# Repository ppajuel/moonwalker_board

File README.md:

# moonwalker_board
Expansion board compatible with [Raspberry Pi 1 Modelo B](https://www.raspberrypi.org/products/model-b/)
 and [IGEP NEW YORK](https://isee.biz/products/igep-expansion-boards/igep-new-york) to control a RC CAR. Board Layout has been adapted to suite with [Nikko Mega Dominator](http://nikkoevolution.fr/voitures_et_pieces/568/Nikko-Mega-Dominator.html), but can be easily adaptable to another RC Car. Its features are:

* ATmega328 microcontroller: control all expansion board functionalities.
* Raspberry or IGEP boards (optional): control microcontroller through serial port.
* GPS expansion bus: [Adafruit Ultimate GPS Breakout](https://www.adafruit.com/product/746).
* Compass and accelerometer expansion bus: [Triple-axis Accelerometer+Magnetometer (Compass) Board - LSM303)](https://www.adafruit.com/product/1120).
* Gauge battery circuit.
* Servo and brushed motor drivers.
* Two independent power trees for electric motors and sensors&control.
* Atmega programer header.
* Hex segment display.

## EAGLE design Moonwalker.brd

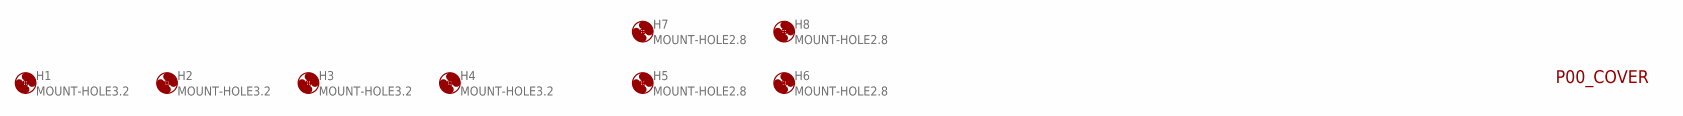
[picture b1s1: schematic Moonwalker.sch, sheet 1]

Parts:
H1, H2, H3, H4: MOUNT-HOLE3.2; 3,2
H5, H6, H7, H8: MOUNT-HOLE2.8; 2,8

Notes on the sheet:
P00_COVER

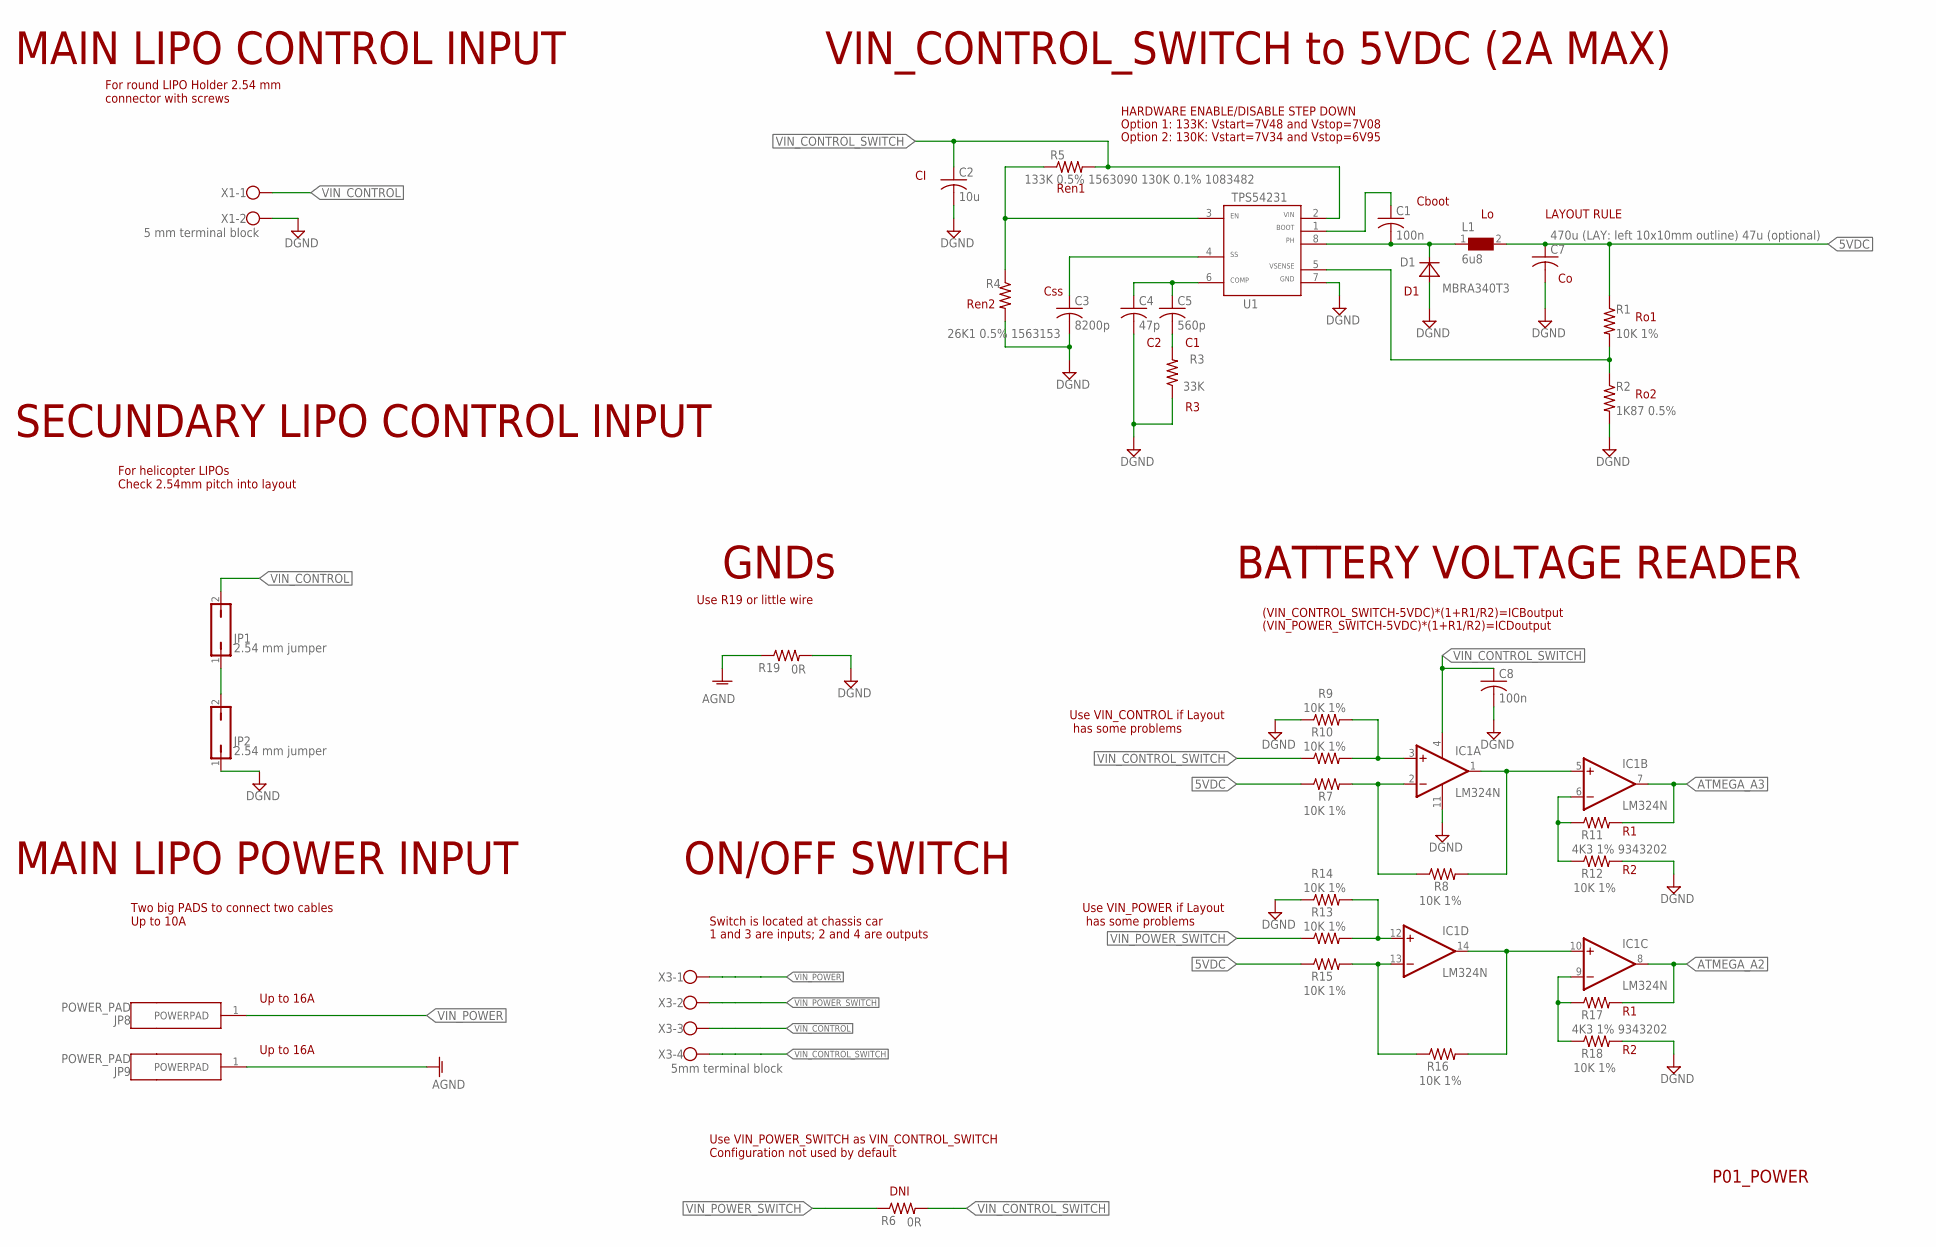
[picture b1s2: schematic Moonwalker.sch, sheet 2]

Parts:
C1: 100n; C075-032X103
C2: 10u; C025-050X050
C3: 8200p; C1206
C4: 47p; C050-024X044
C5: 560p; C1206
C7: 470u (LAY: left 10x10mm outline) 47u (optional); C050-075X075
C8: 100n; C050-024X044
D1: MBRA340T3; SMA
IC1: LM324N; DIL14
JP1, JP2: 2.54 mm jumper; JP1
JP8, JP9: POWER_PAD
L1: 6u8; WE-PD_7332/7345_PLASTIC_BASE
R1, R7, R8, R9, R10, R12, R13, R14, R15, R16, R18: 10K 1%; 0309/10
R2: 1K87 0.5%; 0309/10
R3: 33K; 0309/10
R4: 26K1 0.5% 1563153; 0309/10
R5: 133K 0.5% 1563090 130K 0.1% 1083482; 0309/10
R6, R19: 0R; 0309/10
R11, R17: 4K3 1% 9343202; 0309/10
U1: TPS54231SO8; SO8
X1: 5 mm terminal block; W237-102
X3: 5mm terminal block; W237-4

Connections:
5VDC: C7.1, L1.2, R1.1, R7.1, R15.1; also elsewhere on the board
AGND: JP9.1, R19.1; also elsewhere on the board
ATMEGA_A2: IC1.8 (OUT), R17.2; also elsewhere on the board
ATMEGA_A3: IC1.7 (OUT), R11.2; also elsewhere on the board
DGND: C2.2, C3.2, C4.2, C7.2, C8.2, D1.A, IC1.11 (V-), JP2.1, R2.2, R3.1, R4.2, R9.1, R12.2, R14.1, R18.2, R19.2, U1.7, X1.2; also elsewhere on the board
unnamed: C4.1, C5.1, U1.6
unnamed: C5.2, R3.2
unnamed: R4.1, R5.1, U1.3
unnamed: C3.1, U1.4
unnamed: C1.2, D1.C, L1.1, U1.8
unnamed: C1.1, U1.1
unnamed: R1.2, R2.1, U1.5
unnamed: JP1.1, JP2.2
unnamed: IC1.3 (+IN), R9.2, R10.2
unnamed: IC1.2 (-IN), R7.2, R8.1
unnamed: IC1.12 (+IN), R13.2, R14.2
unnamed: IC1.13 (-IN), R15.2, R16.1
unnamed: IC1.10 (+IN), IC1.14 (OUT), R16.2
unnamed: IC1.1 (OUT), IC1.5 (+IN), R8.2
unnamed: IC1.6 (-IN), R11.1, R12.1
unnamed: IC1.9 (-IN), R17.1, R18.1
VIN_CONTROL: JP1.2, X1.1, X3.3
VIN_CONTROL_SWITCH: C2.1, C8.1, IC1.4 (V+), R5.2, R6.2, R10.1, U1.2, X3.4
VIN_POWER: JP8.1, X3.1; also elsewhere on the board
VIN_POWER_SWITCH: R6.1, R13.1, X3.2

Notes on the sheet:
P01_POWER
Cboot
VIN_CONTROL_SWITCH to 5VDC (2A MAX)
Option 2: 130K: Vstart=7V34 and Vstop=6V95
Option 1: 133K: Vstart=7V48 and Vstop=7V08
HARDWARE ENABLE/DISABLE STEP DOWN
Ren2
Ren1
Css
Ro1
Ro2
MAIN LIPO CONTROL INPUT
SECUNDARY LIPO CONTROL INPUT
For round LIPO Holder 2.54 mm connector with screws
For helicopter LIPOs Check 2.54mm pitch into layout
MAIN LIPO POWER INPUT
Two big PADS to connect two cables Up to 10A
Use VIN_POWER_SWITCH as VIN_CONTROL_SWITCH Configuration not used by default
DNI
BATTERY VOLTAGE READER
ON/OFF SWITCH
(VIN_CONTROL_SWITCH-5VDC)*(1+R1/R2)=ICBoutput
(VIN_POWER_SWITCH-5VDC)*(1+R1/R2)=ICDoutput
GNDs
Switch is located at chassis car
Use VIN_POWER if Layout has some problems
Use VIN_CONTROL if Layout has some problems
Up to 16A
LAYOUT RULE
Use R19 or little wire
1 and 3 are inputs; 2 and 4 are outputs

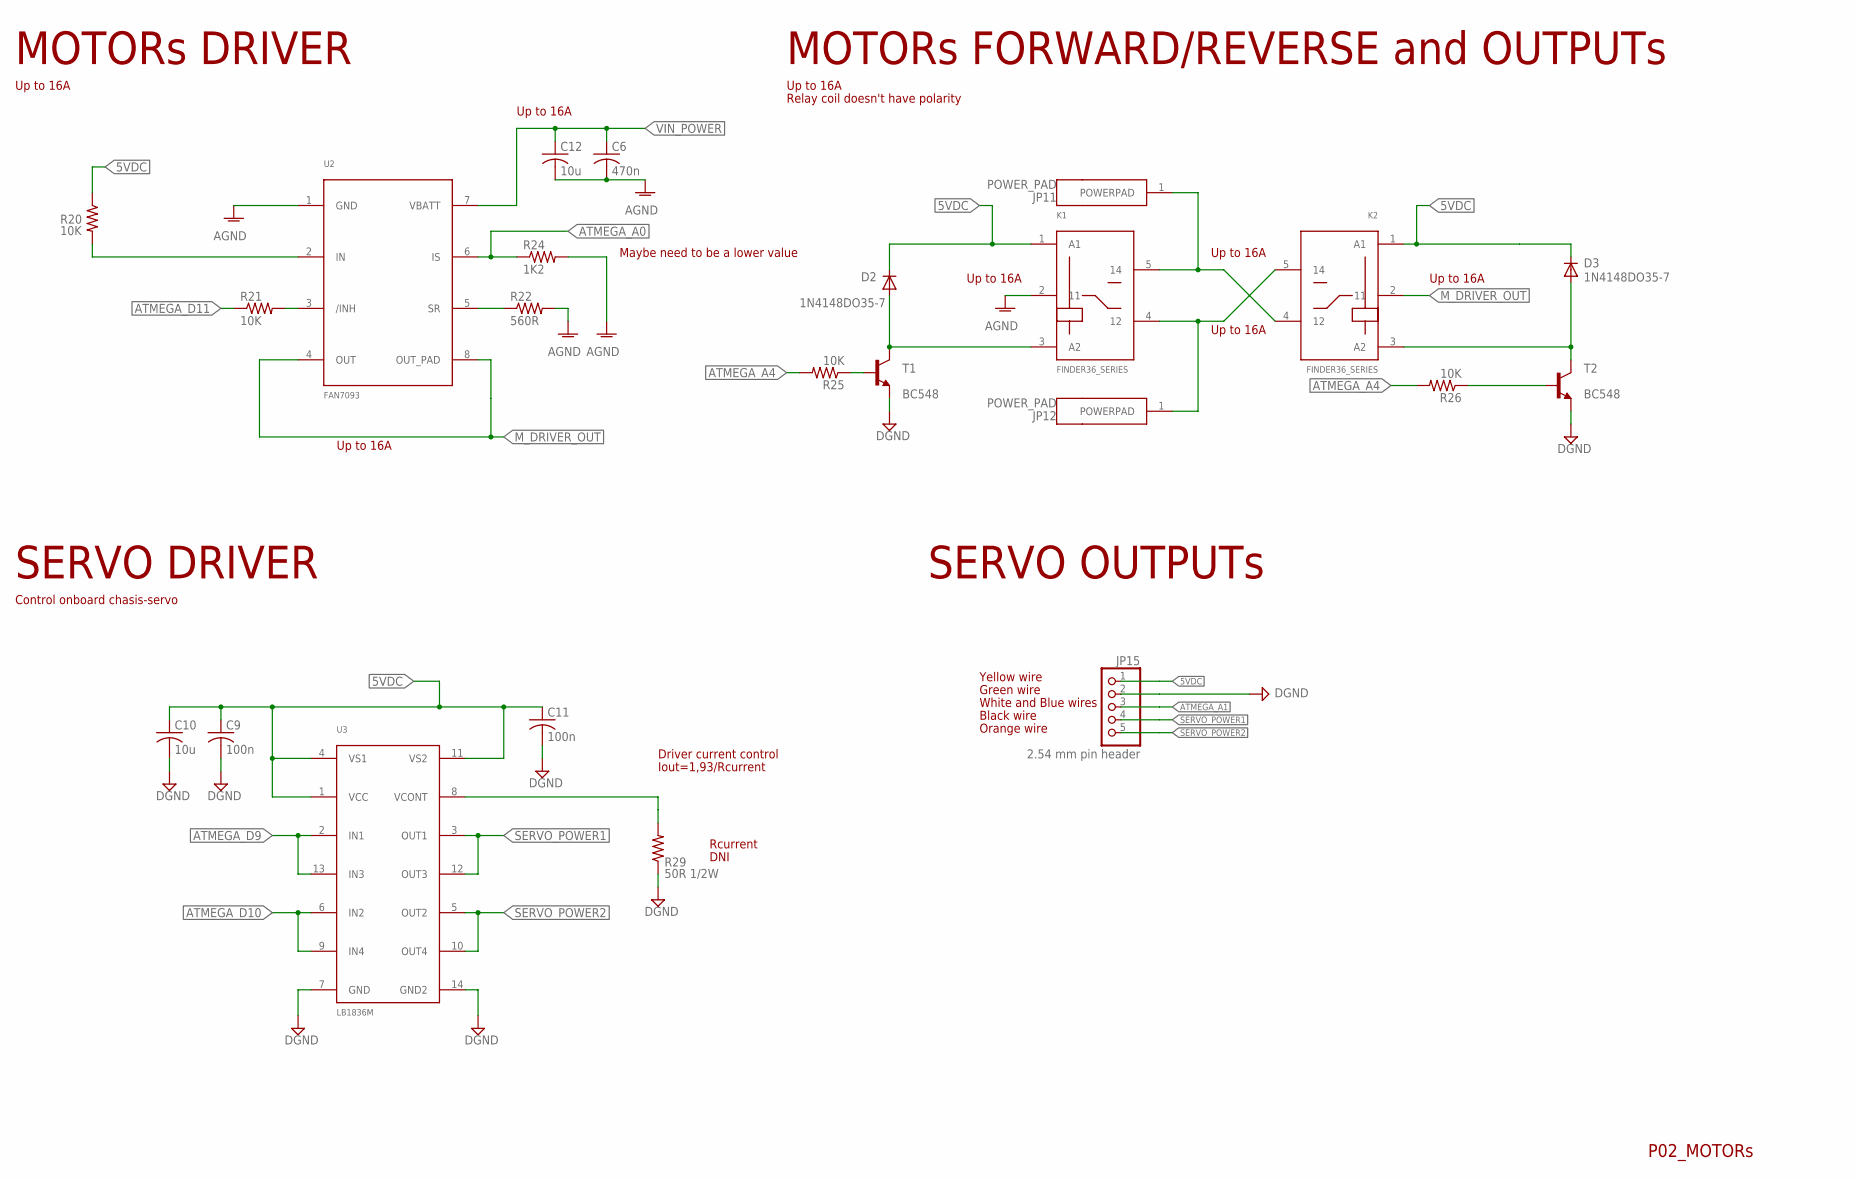
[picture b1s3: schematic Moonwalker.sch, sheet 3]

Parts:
C6: 470n; C050-050X075
C9, C11: 100n; C050-024X044
C10, C12: 10u; C025-050X050
D2, D3: 1N4148DO35-7; DO35-7
JP11, JP12: POWER_PAD
JP15: 2.54 mm pin header; 1X05/90
K1, K2: FINDER36_SERIES; FINDERSERIE36
R20, R21, R25, R26: 10K; 0309/10
R22: 560R; 0309/10
R24: 1K2; 0411/12
R29: 50R 1/2W; 0411/12
T1, T2: BC548; TO92-CBE
U2: FAN7093; TO263
U3: LB1836M; SOIC14W

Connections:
5VDC: C9.1, C10.1, C11.1, D2.C, D3.C, JP15.1, K1.1 (A1), K2.1 (A1), R20.1, U3.1 (VCC), U3.4 (VS1), U3.11 (VS2); also elsewhere on the board
AGND: C6.2, C12.2, K1.2 (11), R22.2, R24.2, U2.1 (GND); also elsewhere on the board
ATMEGA_A0: R24.1, U2.6 (IS); also elsewhere on the board
ATMEGA_A1: JP15.3; also elsewhere on the board
ATMEGA_A4: R25.2, R26.2; also elsewhere on the board
ATMEGA_D9: U3.2 (IN1), U3.13 (IN3); also elsewhere on the board
ATMEGA_D10: U3.6 (IN2), U3.9 (IN4); also elsewhere on the board
ATMEGA_D11: R21.1; also elsewhere on the board
DGND: C9.2, C10.2, C11.2, JP15.2, R29.1, T1.E, T2.E, U3.7 (GND), U3.14 (GND2); also elsewhere on the board
M_DRIVER_OUT: K2.2 (11), U2.4 (OUT), U2.8 (OUT_PAD)
unnamed: R29.2, U3.8 (VCONT)
unnamed: JP11.1, K1.5 (14), K2.4 (12)
unnamed: R22.1, U2.5 (SR)
unnamed: R20.2, U2.2 (IN)
unnamed: R21.2, U2.3 (/INH)
unnamed: JP12.1, K1.4 (12), K2.5 (14)
unnamed: D2.A, K1.3 (A2), T1.C
unnamed: D3.A, K2.3 (A2), T2.C
unnamed: R26.1, T2.B
unnamed: R25.1, T1.B
SERVO_POWER1: JP15.4, U3.3 (OUT1), U3.12 (OUT3)
SERVO_POWER2: JP15.5, U3.5 (OUT2), U3.10 (OUT4)
VIN_POWER: C6.1, C12.1, U2.7 (VBATT); also elsewhere on the board

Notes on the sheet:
P02_MOTORs
MOTORs DRIVER
Up to 16A
MOTORs FORWARD/REVERSE and OUTPUTs
SERVO DRIVER
Control onboard chasis-servo
Driver current control
Iout=1,93/Rcurrent
Rcurrent
DNI
SERVO OUTPUTs
Yellow wire
Green wire
White and Blue wires
Black wire
Orange wire
Maybe need to be a lower value
Relay coil doesn't have polarity

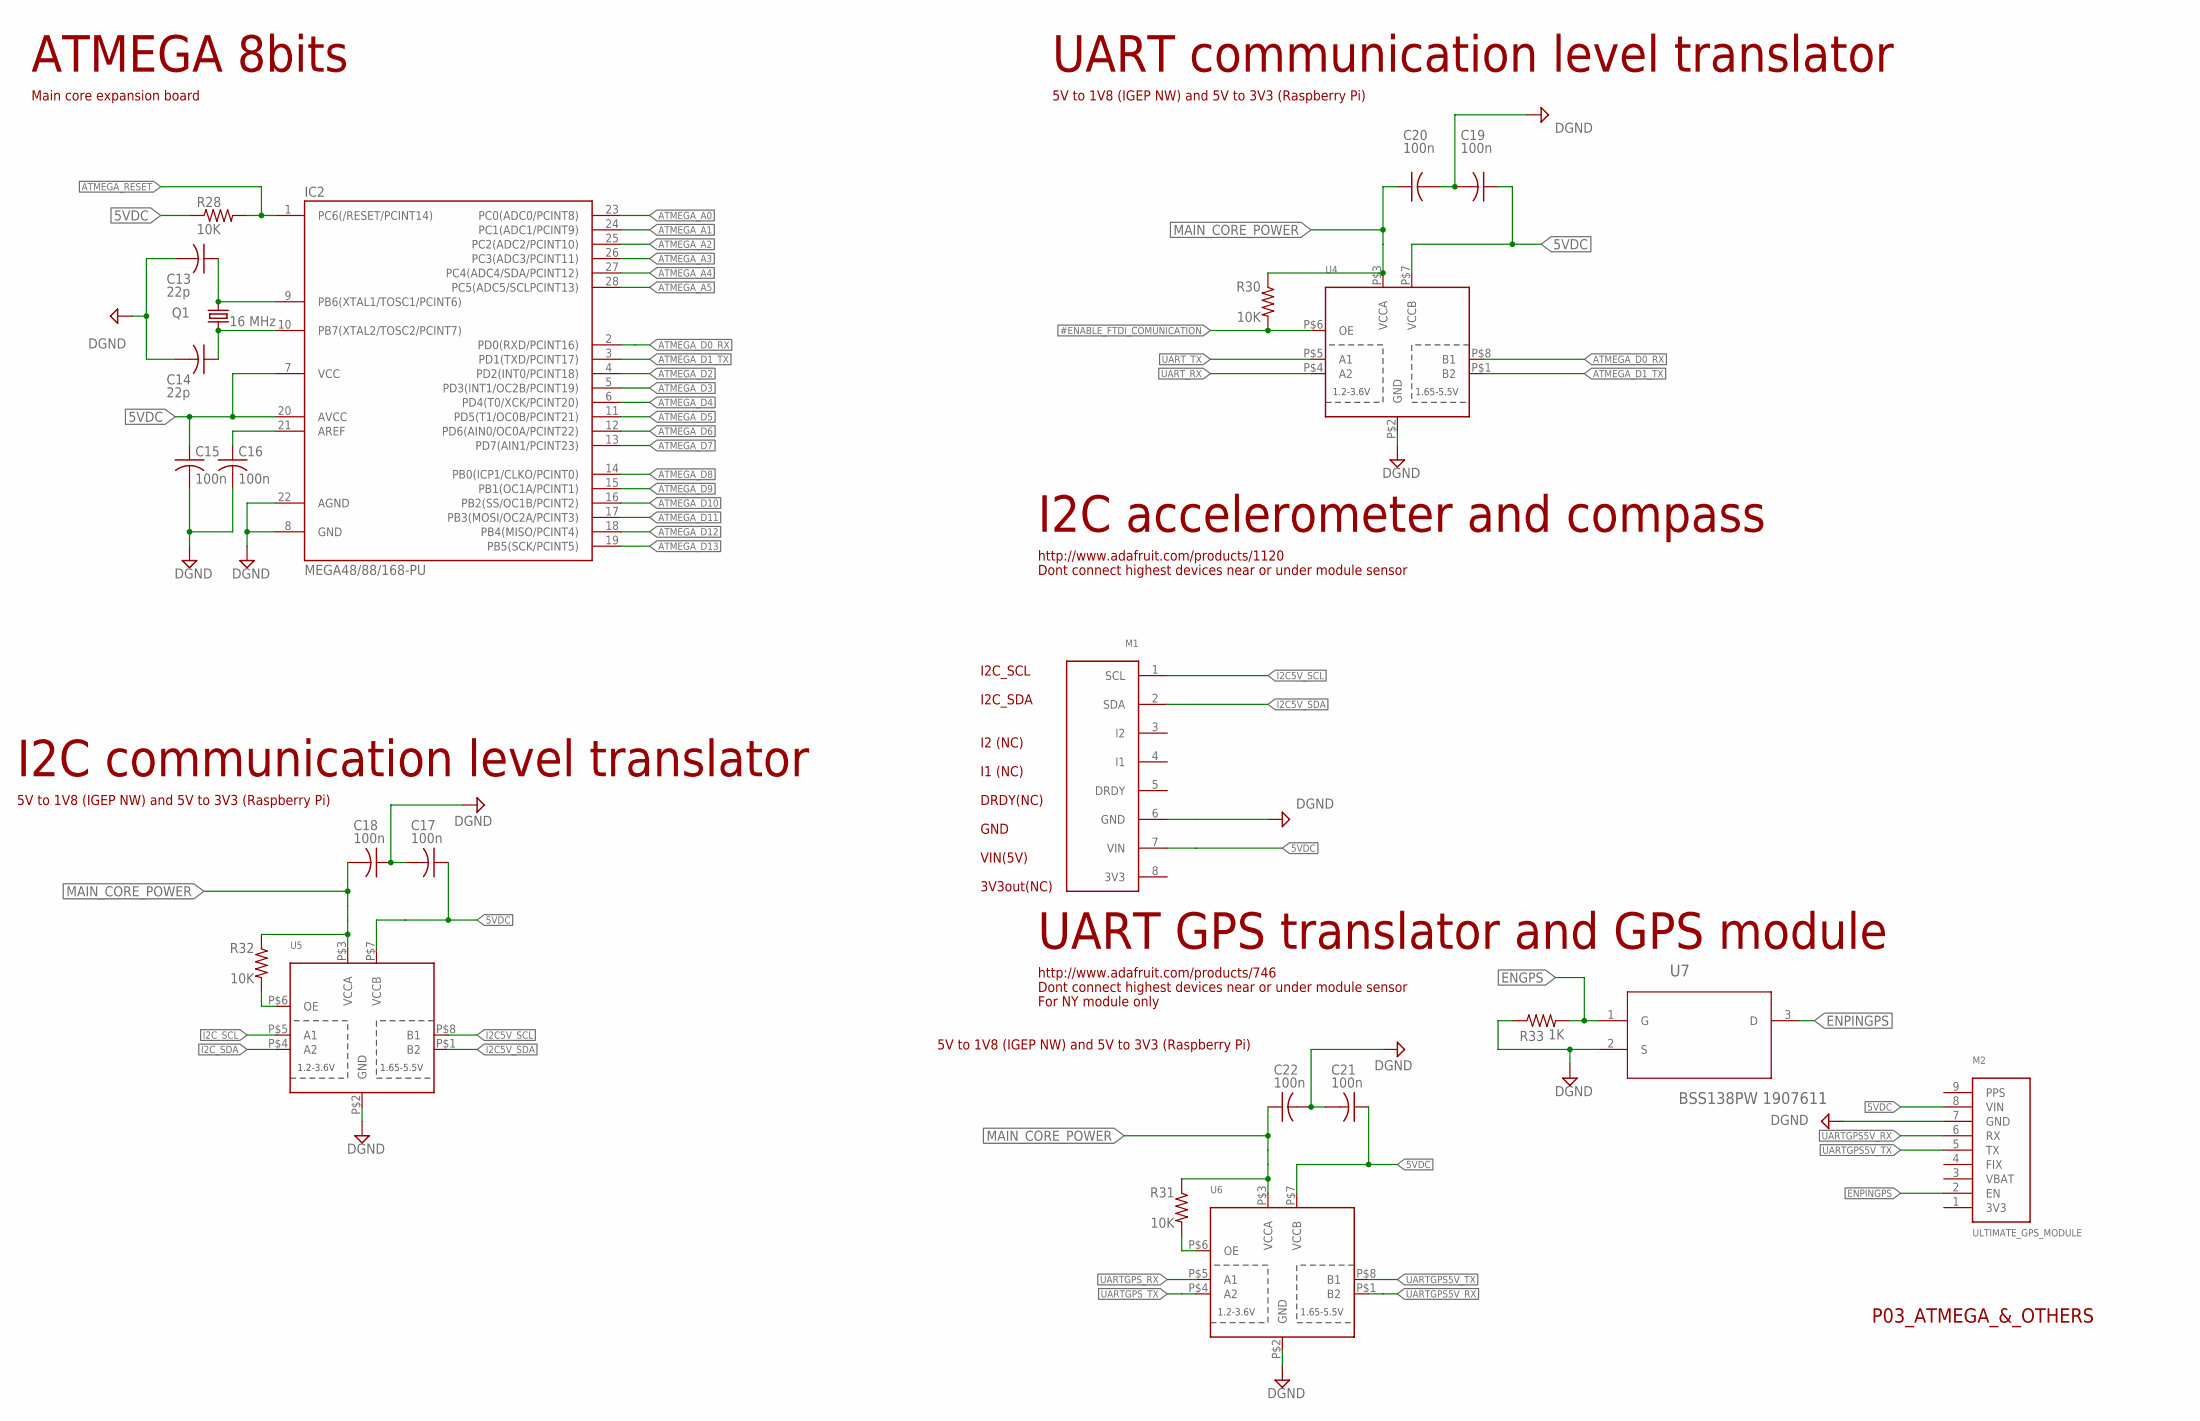
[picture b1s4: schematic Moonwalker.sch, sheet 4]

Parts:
C13, C14: 22p; C050-024X044
C15, C16, C17, C18, C19, C20, C21, C22: 100n; C050-024X044
IC2: MEGA48/88/168-PU; DIL28-3
M1: COMPASS_&_ACCELEROMETER_ADAFRUIT_LSM303
M2: ULTIMATE_GPS_MODULE
Q1: 16 MHz; HC49/S
R28, R30, R31, R32: 10K; 0309/10
R33: 1K; 0309/10
U4, U5, U6: TXS0102; VFSOP-8
U7: BSS138PW 1907611; SOT65P210X110-3N

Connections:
5VDC: C15.1, C17.1, C19.1, C21.1, IC2.7 (VCC), IC2.20 (AVCC), M1.7 (VIN), M2.8 (VIN), R28.1, U4.P$7 (VCCB), U5.P$7 (VCCB), U6.P$7 (VCCB); also elsewhere on the board
#ENABLE_FTDI_COMUNICATION: R30.2, U4.P$6 (OE); also elsewhere on the board
ATMEGA_A0: IC2.23 (PC0(ADC0/PCINT8)); also elsewhere on the board
ATMEGA_A1: IC2.24 (PC1(ADC1/PCINT9)); also elsewhere on the board
ATMEGA_A2: IC2.25 (PC2(ADC2/PCINT10)); also elsewhere on the board
ATMEGA_A3: IC2.26 (PC3(ADC3/PCINT11)); also elsewhere on the board
ATMEGA_A4: IC2.27 (PC4(ADC4/SDA/PCINT12)); also elsewhere on the board
ATMEGA_A5: IC2.28 (PC5(ADC5/SCLPCINT13)); also elsewhere on the board
ATMEGA_D0_RX: IC2.2 (PD0(RXD/PCINT16)), U4.P$8 (B1); also elsewhere on the board
ATMEGA_D1_TX: IC2.3 (PD1(TXD/PCINT17)), U4.P$1 (B2); also elsewhere on the board
ATMEGA_D2: IC2.4 (PD2(INT0/PCINT18)); also elsewhere on the board
ATMEGA_D3: IC2.5 (PD3(INT1/OC2B/PCINT19)); also elsewhere on the board
ATMEGA_D4: IC2.6 (PD4(T0/XCK/PCINT20)); also elsewhere on the board
ATMEGA_D5: IC2.11 (PD5(T1/OC0B/PCINT21)); also elsewhere on the board
ATMEGA_D6: IC2.12 (PD6(AIN0/OC0A/PCINT22)); also elsewhere on the board
ATMEGA_D7: IC2.13 (PD7(AIN1/PCINT23)); also elsewhere on the board
ATMEGA_D8: IC2.14 (PB0(ICP1/CLKO/PCINT0)); also elsewhere on the board
ATMEGA_D9: IC2.15 (PB1(OC1A/PCINT1)); also elsewhere on the board
ATMEGA_D10: IC2.16 (PB2(SS/OC1B/PCINT2)); also elsewhere on the board
ATMEGA_D11: IC2.17 (PB3(MOSI/OC2A/PCINT3)); also elsewhere on the board
ATMEGA_D12: IC2.18 (PB4(MISO/PCINT4)); also elsewhere on the board
ATMEGA_D13: IC2.19 (PB5(SCK/PCINT5)); also elsewhere on the board
ATMEGA_RESET: IC2.1 (PC6(/RESET/PCINT14)), R28.2; also elsewhere on the board
DGND: C13.2, C14.2, C15.2, C16.2, C17.2, C18.1, C19.2, C20.2, C21.2, C22.2, IC2.8 (GND), IC2.22 (AGND), M1.6 (GND), M2.7 (GND), R33.1, U4.P$2 (GND), U5.P$2 (GND), U6.P$2 (GND), U7.2 (S); also elsewhere on the board
ENGPS: R33.2, U7.1 (G); also elsewhere on the board
ENPINGPS: M2.2 (EN), U7.3 (D)
I2C5V_SCL: M1.1 (SCL), U5.P$8 (B1)
I2C5V_SDA: M1.2 (SDA), U5.P$1 (B2)
I2C_SCL: U5.P$5 (A1); also elsewhere on the board
I2C_SDA: U5.P$4 (A2); also elsewhere on the board
MAIN_CORE_POWER: C18.2, C20.1, C22.1, R30.1, R31.1, R32.1, U4.P$3 (VCCA), U5.P$3 (VCCA), U6.P$3 (VCCA); also elsewhere on the board
unnamed: C13.1, IC2.9 (PB6(XTAL1/TOSC1/PCINT6)), Q1.2
unnamed: C14.1, IC2.10 (PB7(XTAL2/TOSC2/PCINT7)), Q1.1
unnamed: C16.1, IC2.21 (AREF)
unnamed: R32.2, U5.P$6 (OE)
unnamed: R31.2, U6.P$6 (OE)
UARTGPS5V_RX: M2.6 (RX), U6.P$1 (B2)
UARTGPS5V_TX: M2.5 (TX), U6.P$8 (B1)
UARTGPS_RX: U6.P$5 (A1); also elsewhere on the board
UARTGPS_TX: U6.P$4 (A2); also elsewhere on the board
UART_RX: U4.P$4 (A2); also elsewhere on the board
UART_TX: U4.P$5 (A1); also elsewhere on the board

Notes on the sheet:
P03_ATMEGA_&_OTHERS
ATMEGA 8bits
Main core expansion board
UART communication level translator
5V to 1V8 (IGEP NW) and 5V to 3V3 (Raspberry Pi)
I2C communication level translator
I2C accelerometer and compass
http://www.adafruit.com/products/1120
Dont connect highest devices near or under module sensor
I2C_SCL
I2C_SDA
I2 (NC)
I1 (NC)
DRDY(NC)
GND
VIN(5V)
3V3out(NC)
UART GPS translator and GPS module
http://www.adafruit.com/products/746
For NY module only

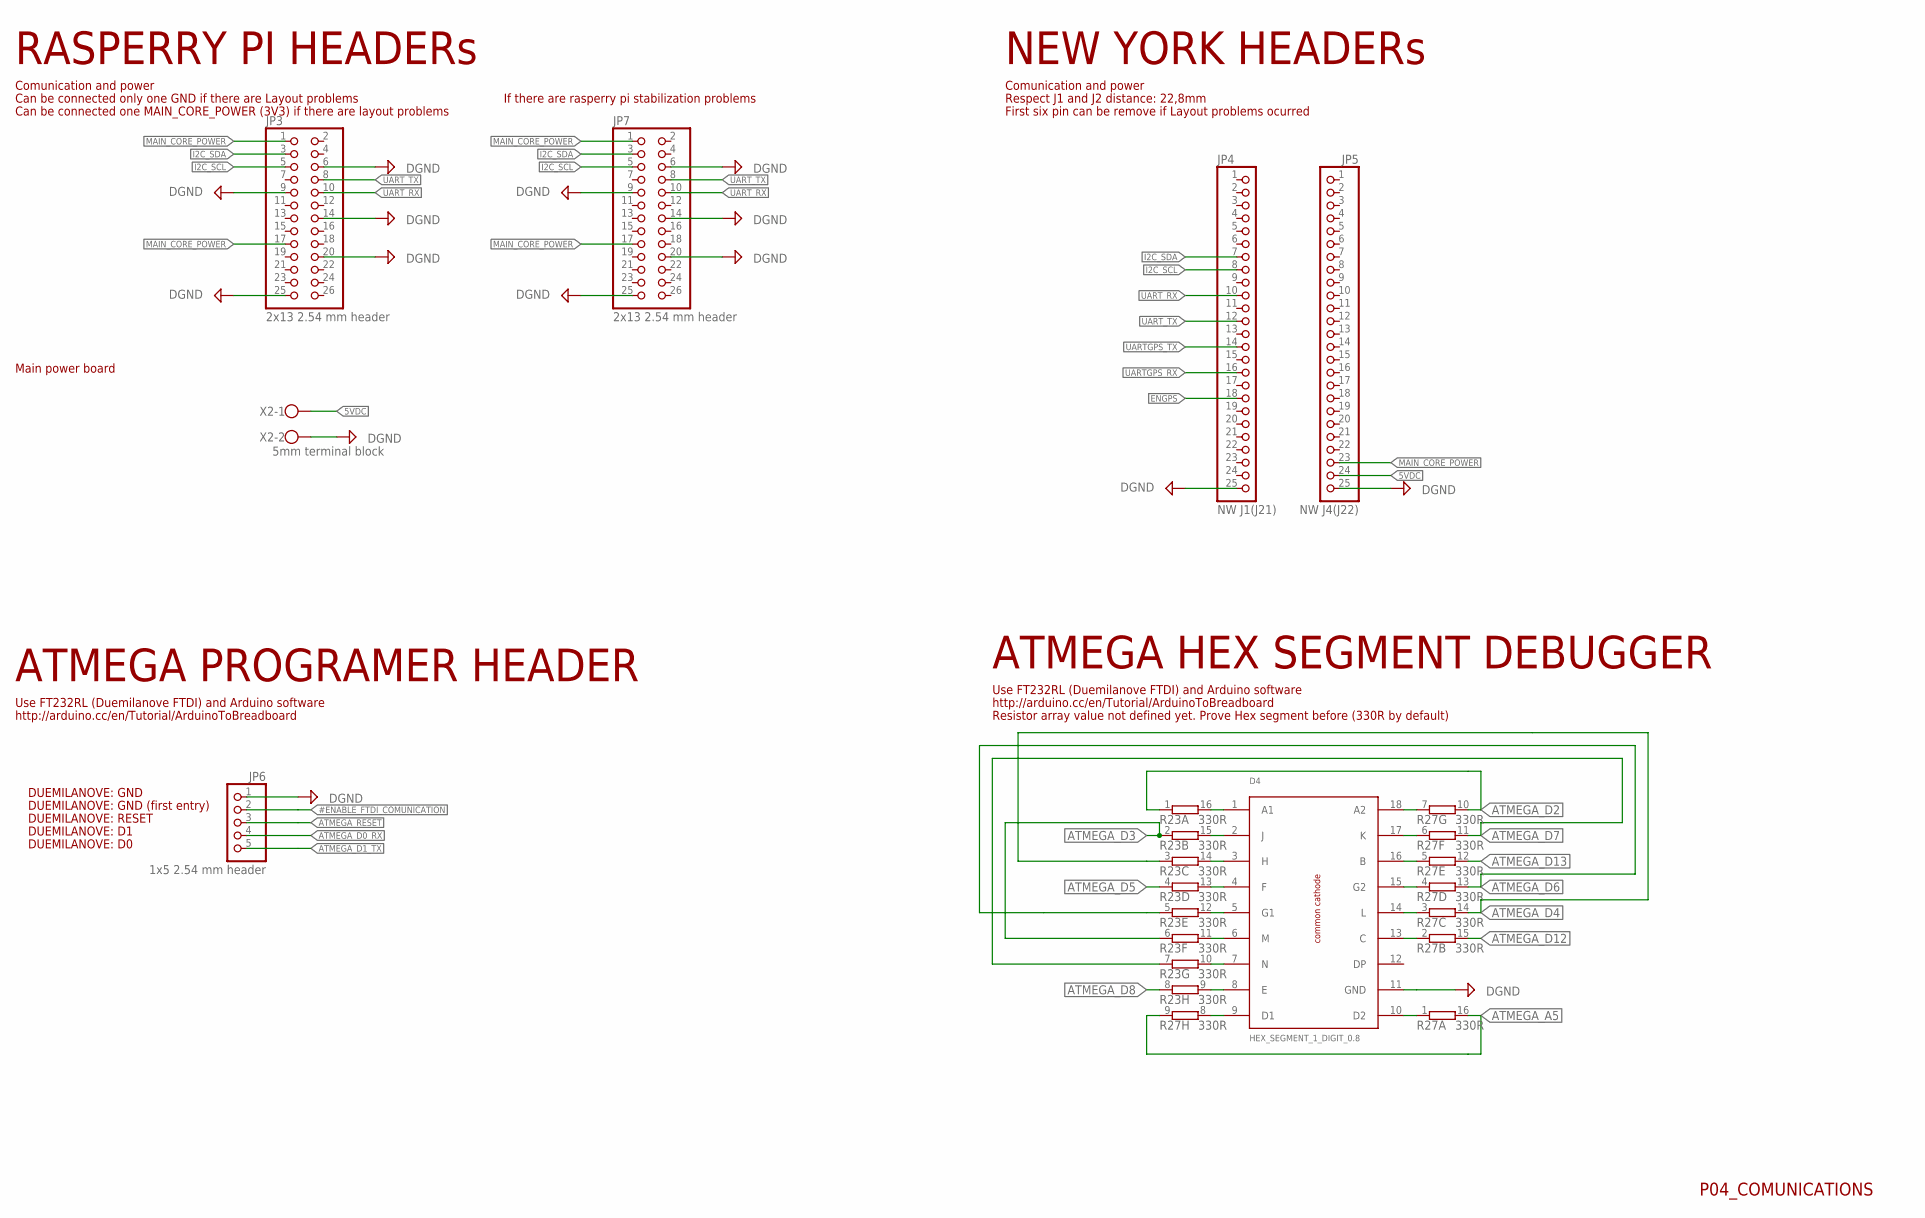
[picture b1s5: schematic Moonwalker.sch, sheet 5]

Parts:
D4: HEX_SEGMENT_1_DIGIT_0.8
JP3, JP7: 2x13 2.54 mm header; 2X13
JP4: NW J1(J21); 1X25
JP5: NW J4(J22); 1X25
JP6: 1x5 2.54 mm header; 1X05/90
R23, R27: 330R; 4816P
X2: 5mm terminal block; W237-102

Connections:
5VDC: JP5.24, X2.1; also elsewhere on the board
#ENABLE_FTDI_COMUNICATION: JP6.2; also elsewhere on the board
ATMEGA_A5: R27.9 (2), R27.16 (2); also elsewhere on the board
ATMEGA_D0_RX: JP6.4; also elsewhere on the board
ATMEGA_D1_TX: JP6.5; also elsewhere on the board
ATMEGA_D2: R23.1, R27.10 (2); also elsewhere on the board
ATMEGA_D3: R23.2 (1), R23.6 (1); also elsewhere on the board
ATMEGA_D4: R23.3 (1), R27.14 (2); also elsewhere on the board
ATMEGA_D5: R23.4 (1); also elsewhere on the board
ATMEGA_D6: R23.5 (1), R27.13 (2); also elsewhere on the board
ATMEGA_D7: R23.7 (1), R27.11 (2); also elsewhere on the board
ATMEGA_D8: R23.8 (1); also elsewhere on the board
ATMEGA_D12: R27.15 (2); also elsewhere on the board
ATMEGA_D13: R27.12 (2); also elsewhere on the board
ATMEGA_RESET: JP6.3; also elsewhere on the board
DGND: D4.11 (GND), JP3.6, JP3.9, JP3.14, JP3.20, JP3.25, JP4.25, JP5.25, JP6.1, JP7.6, JP7.9, JP7.14, JP7.20, JP7.25, X2.2; also elsewhere on the board
ENGPS: JP4.18; also elsewhere on the board
I2C_SCL: JP3.5, JP4.8, JP7.5; also elsewhere on the board
I2C_SDA: JP3.3, JP4.7, JP7.3; also elsewhere on the board
MAIN_CORE_POWER: JP3.1, JP3.17, JP5.23, JP7.1, JP7.17; also elsewhere on the board
unnamed: D4.9 (D1), R27.8 (1)
unnamed: D4.1 (A1), R23.16 (2)
unnamed: D4.13 (C), R27.2 (1)
unnamed: D4.2 (J), R23.15 (2)
unnamed: D4.3 (H), R23.14 (2)
unnamed: D4.4 (F), R23.13 (2)
unnamed: D4.5 (G1), R23.12 (2)
unnamed: D4.10 (D2), R27.1
unnamed: D4.6 (M), R23.11 (2)
unnamed: D4.7 (N), R23.10 (2)
unnamed: D4.8 (E), R23.9 (2)
unnamed: D4.18 (A2), R27.7 (1)
unnamed: D4.17 (K), R27.6 (1)
unnamed: D4.16 (B), R27.5 (1)
unnamed: D4.15 (G2), R27.4 (1)
unnamed: D4.14 (L), R27.3 (1)
UARTGPS_RX: JP4.16; also elsewhere on the board
UARTGPS_TX: JP4.14; also elsewhere on the board
UART_RX: JP3.10, JP4.10, JP7.10; also elsewhere on the board
UART_TX: JP3.8, JP4.12, JP7.8; also elsewhere on the board

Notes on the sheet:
P04_COMUNICATIONS
RASPERRY PI HEADERs
Comunication and power
NEW YORK HEADERs
Main power board
Respect J1 and J2 distance: 22,8mm
ATMEGA PROGRAMER HEADER
Use FT232RL (Duemilanove FTDI) and Arduino software
http://arduino.cc/en/Tutorial/ArduinoToBreadboard
First six pin can be remove if Layout problems ocurred
ATMEGA HEX SEGMENT DEBUGGER
DUEMILANOVE: D1
DUEMILANOVE: RESET
DUEMILANOVE: GND
DUEMILANOVE: GND (first entry)
DUEMILANOVE: D0
Can be connected only one GND if there are Layout problems
Can be connected one MAIN_CORE_POWER (3V3) if there are layout problems
Resistor array value not defined yet. Prove Hex segment before (330R by default)
If there are rasperry pi stabilization problems

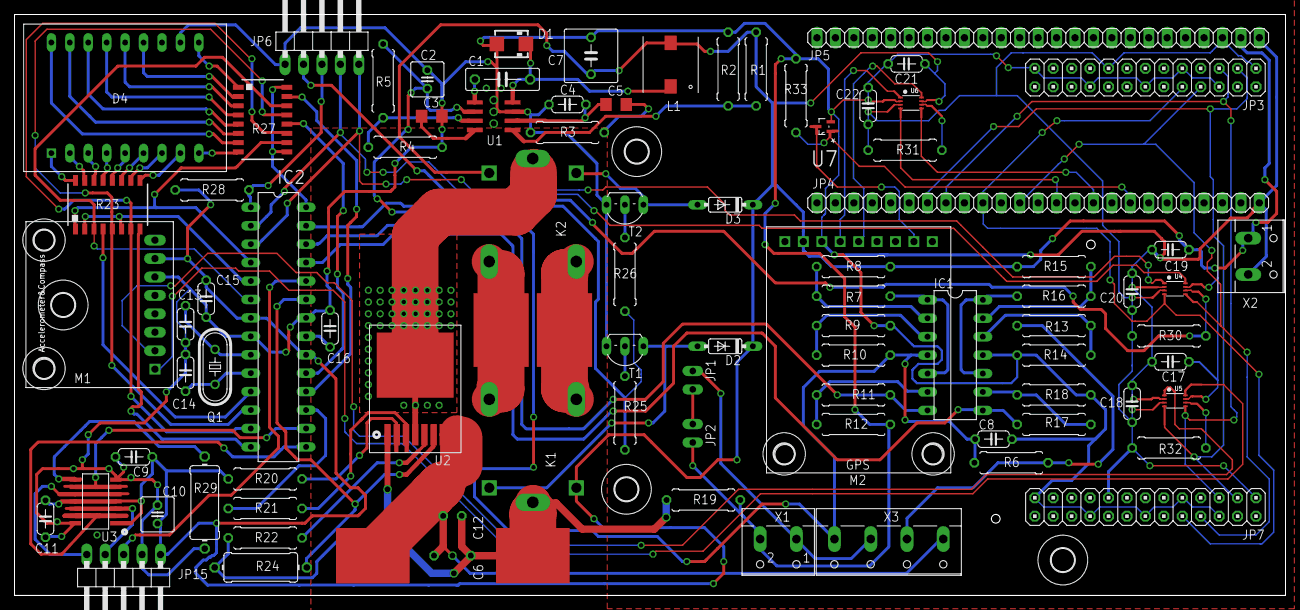
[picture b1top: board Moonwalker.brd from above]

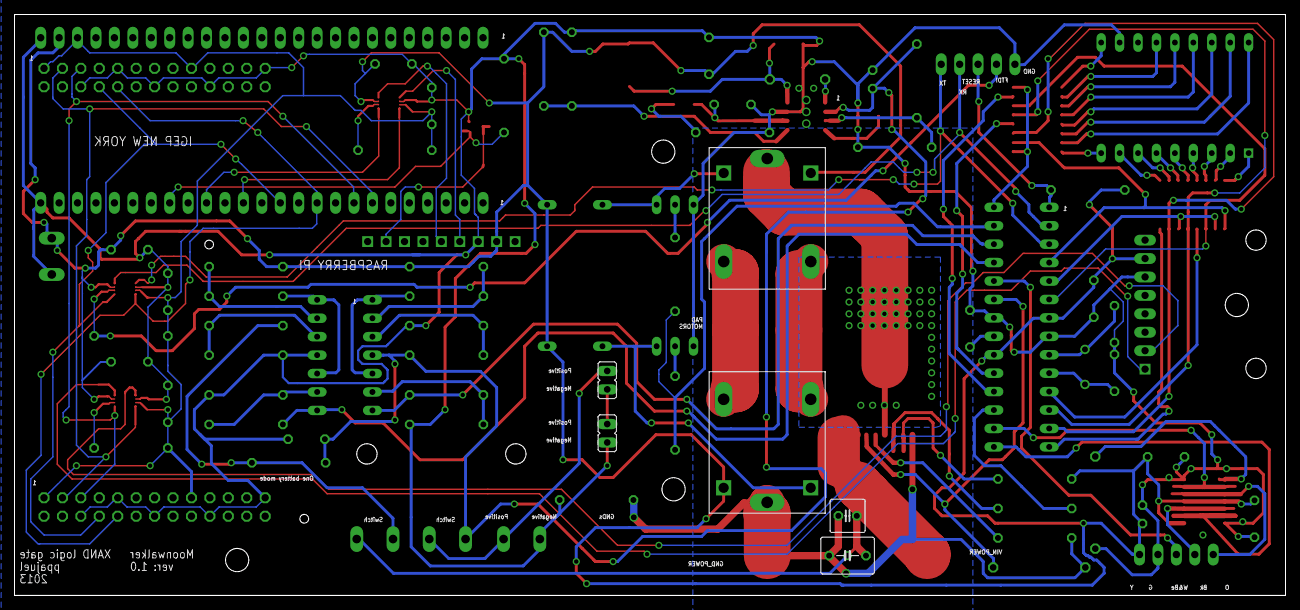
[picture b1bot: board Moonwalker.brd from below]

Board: 2 copper layers, 175.2 x 80.1 mm, 99 parts (6 on the bottom side), 92 nets.

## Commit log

2017-06-04 First schematic and layout release
    sch and brd files contain Eagle schematic and layout respectively
2017-06-04 Add gerbers for release one
2017-06-04 Add schematic pdf for release one
2017-06-04 README.md: Update information
